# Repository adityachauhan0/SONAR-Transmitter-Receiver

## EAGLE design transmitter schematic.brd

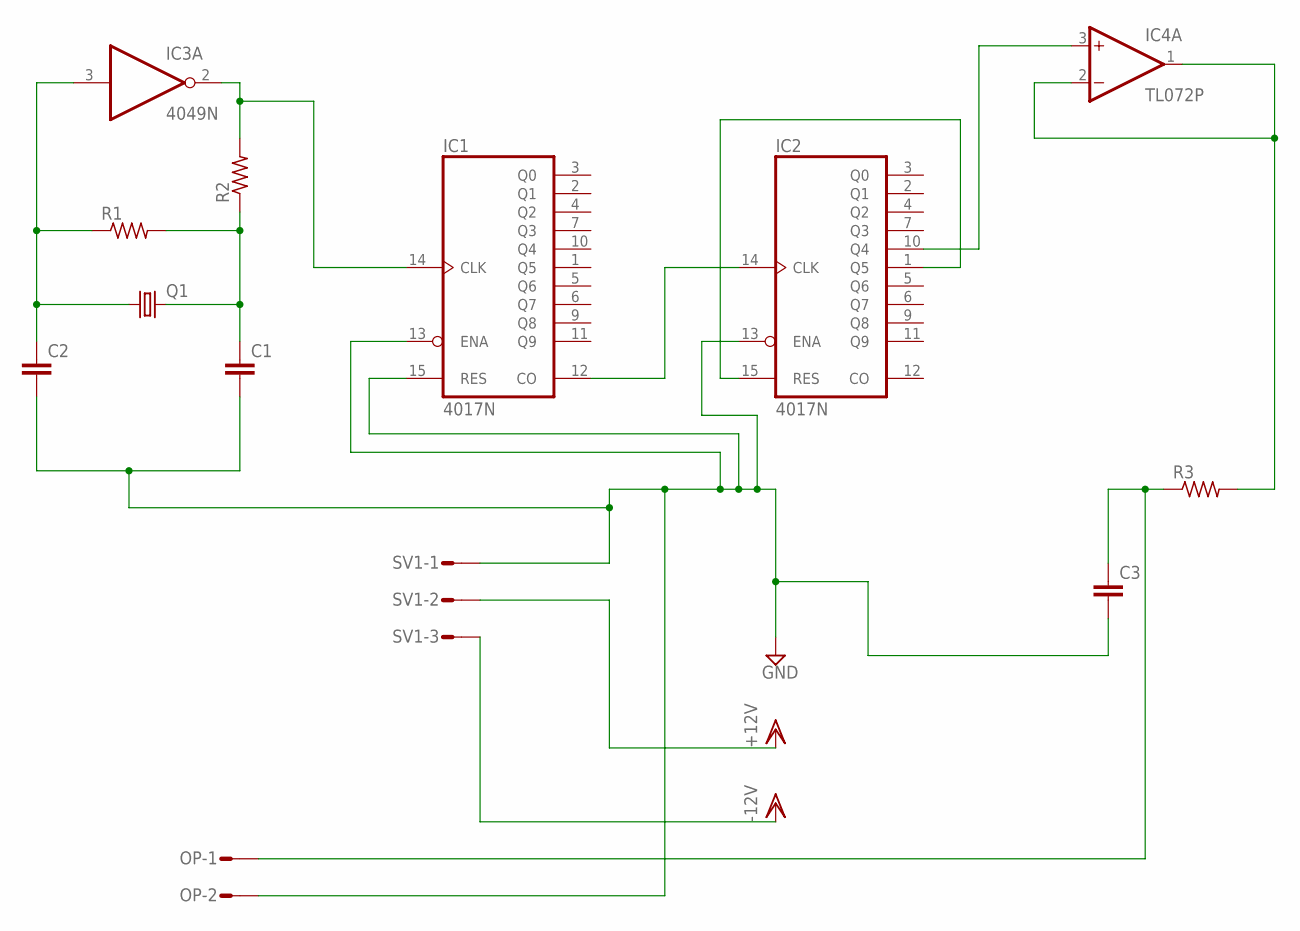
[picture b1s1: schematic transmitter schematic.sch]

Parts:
C1, C2, C3: C5/3.5; C5B3.5
IC1, IC2: 4017N; DIL16
IC3: 4049N; DIL16
IC4: TL072P; DIL08
OP: L02P
Q1: CRYSTALHC49U-V; HC49U-V
R1, R2, R3: R-US_0207/12; 0207/12
SV1: L03P

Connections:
unnamed: IC1.12 (CO), IC2.14 (CLK)
unnamed: C3.1, OP.1, R3.1
unnamed: C1.2, C2.2, C3.2, IC1.13 (ENA), IC1.15 (RES), IC2.13 (ENA), OP.2, SV1.1
unnamed: IC1.14 (CLK), IC3.2 (O), R2.2
unnamed: IC2.1 (Q5), IC2.15 (RES)
unnamed: C2.1, IC3.3 (I), Q1.1, R1.1
unnamed: IC4.1 (OUT), IC4.2 (-IN), R3.2
unnamed: C1.1, Q1.2, R1.2, R2.1
unnamed: IC2.10 (Q4), IC4.3 (+IN)
V+: IC4.8 (V+)
V-: IC4.4 (V-)
VDD: IC1.16 (VDD), IC2.16 (VDD), IC3.1 (VDD), SV1.2, SV1.3
VSS: IC1.8 (VSS), IC2.8 (VSS), IC3.8 (VSS)

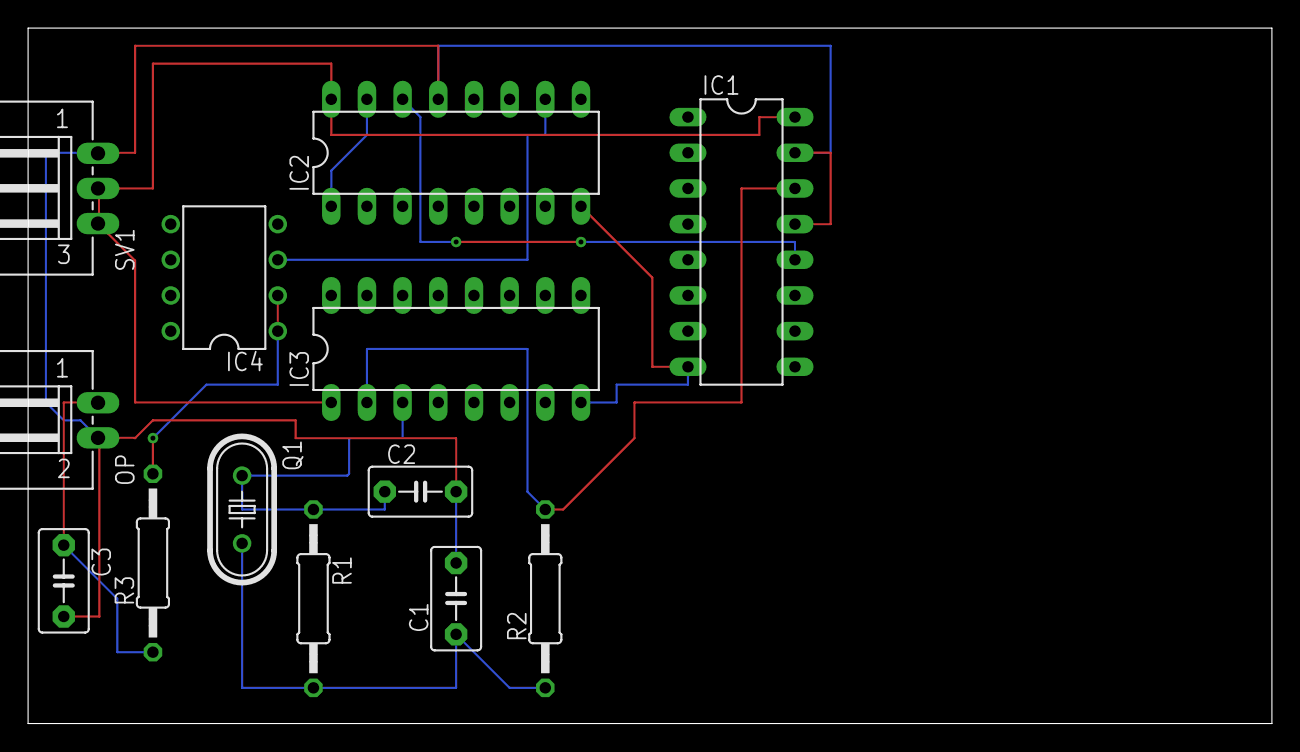
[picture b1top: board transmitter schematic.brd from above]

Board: 2 copper layers, 88.6 x 49.5 mm, 13 parts (0 on the bottom side), 11 nets.
